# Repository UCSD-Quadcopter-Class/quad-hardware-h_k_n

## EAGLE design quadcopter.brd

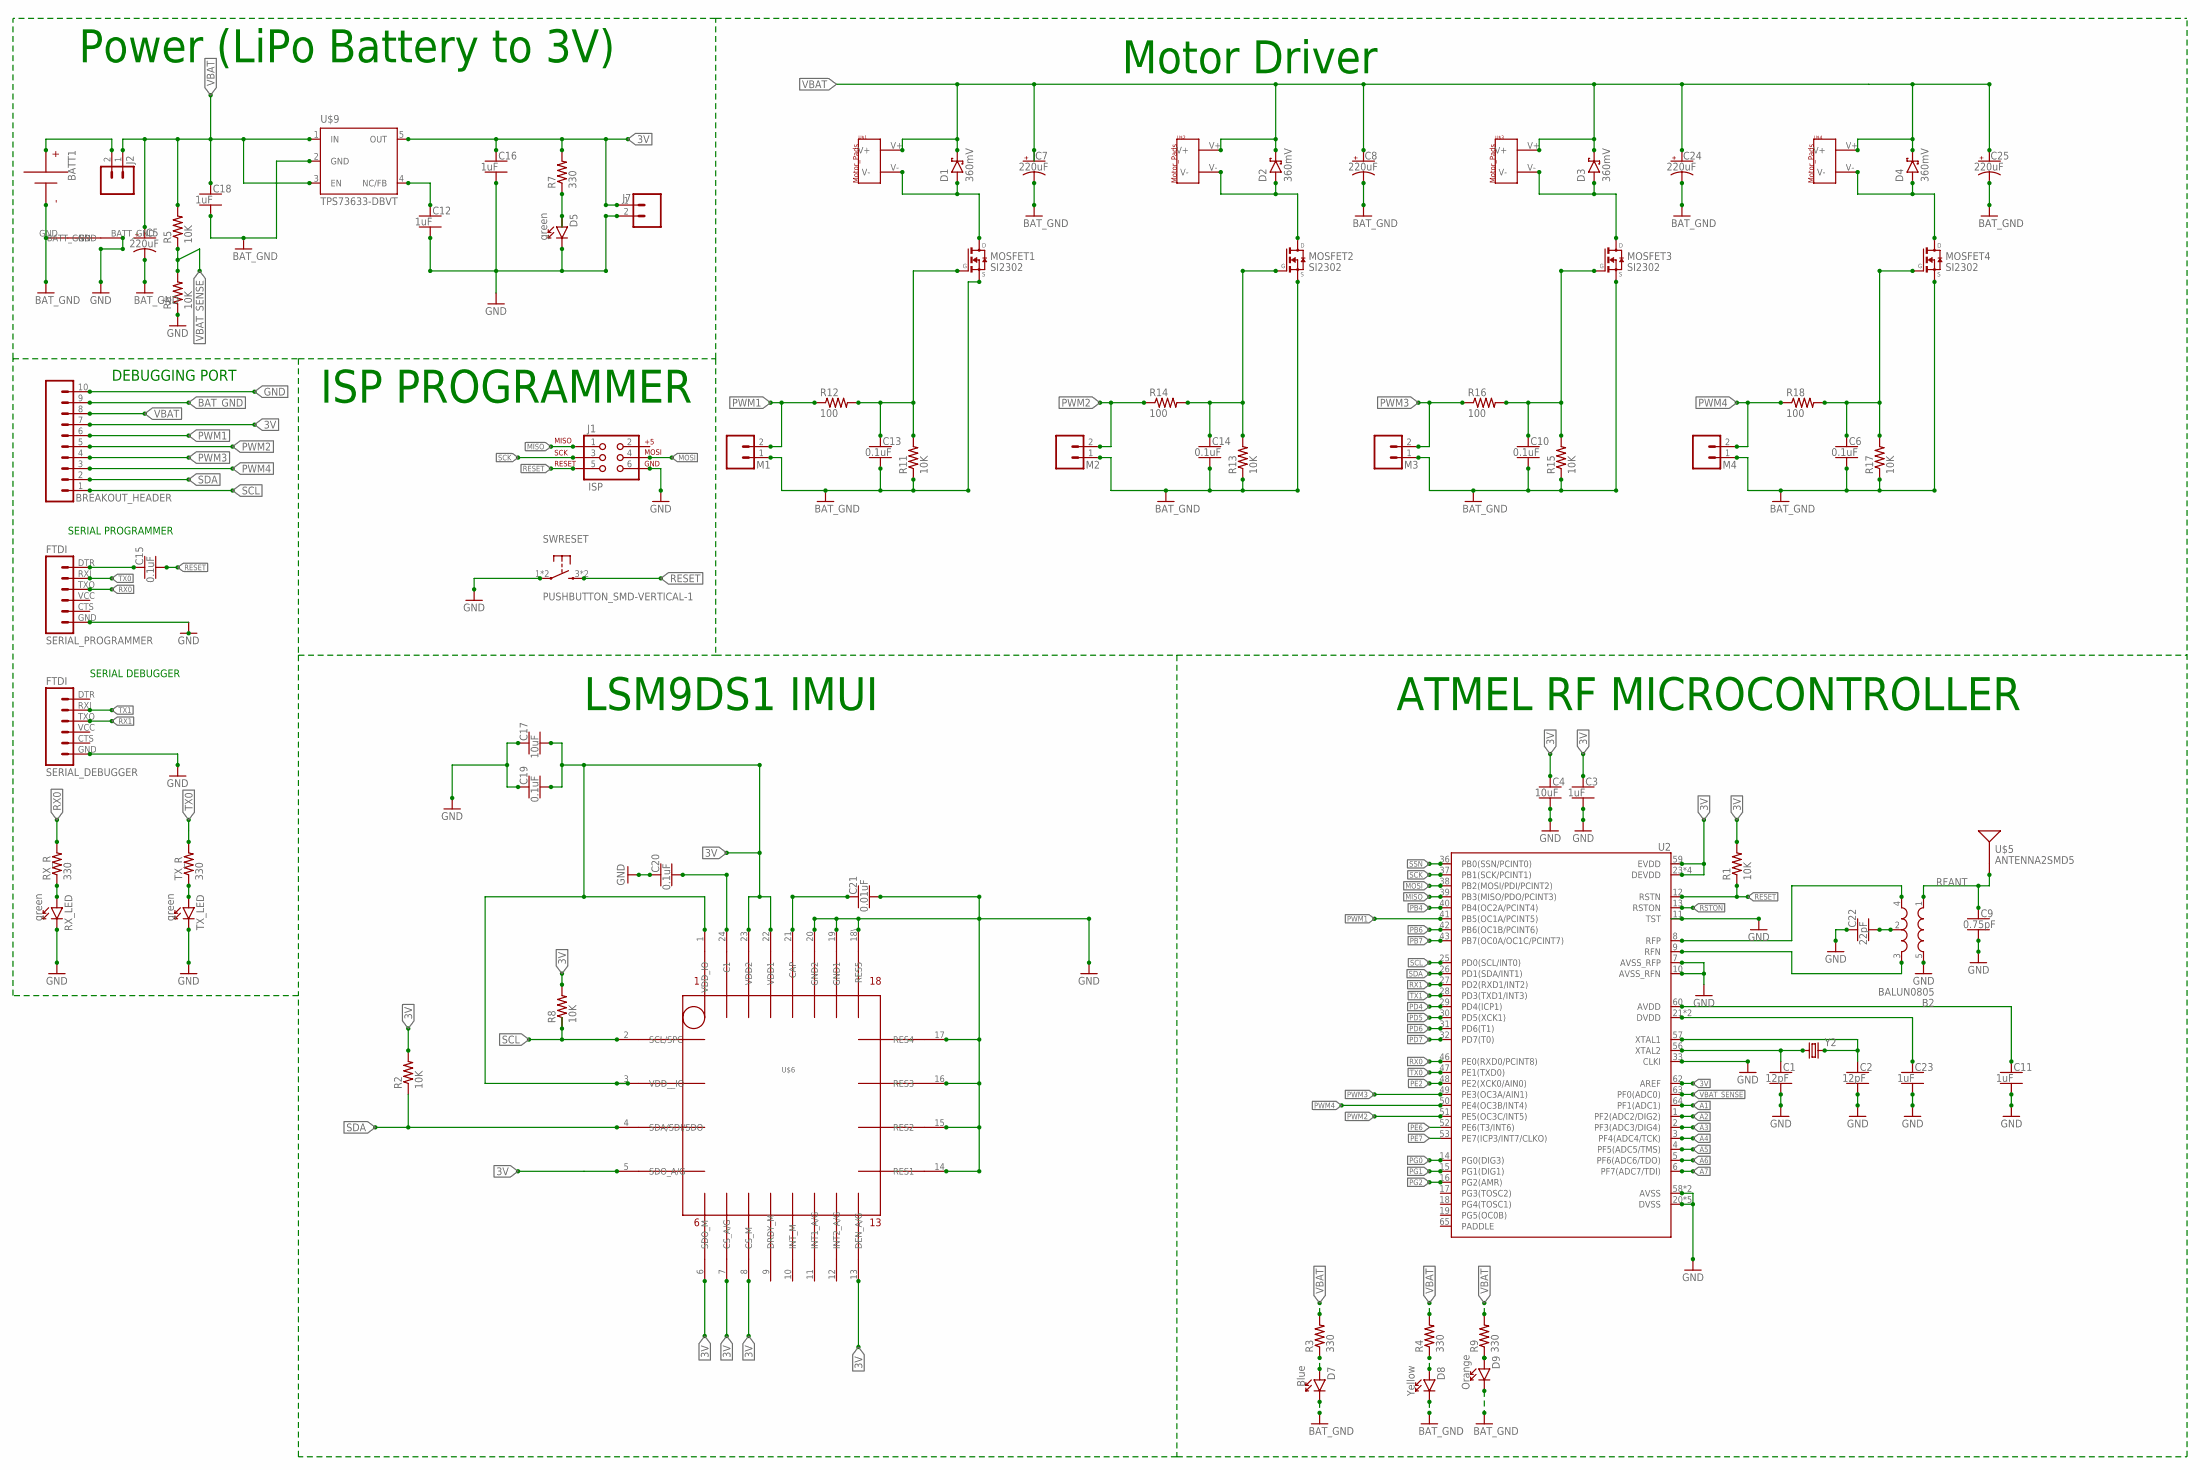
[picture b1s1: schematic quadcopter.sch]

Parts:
B2: BALUN0805; BALUN
BATT1: BATTERY-HUBSAN-W/HOLDER; BATTERY-W/HOLDER-380MAH-HUBSAN
BREAKOUT_HEADER: SIP-10_TH-254X10; HDRV10W63P254_10X1_2540X254H838_HS
C1, C2: 12pF; CAPC2012X140_HS
C3, C11, C12, C16, C18, C23: 1uF; CAPC2012X140_HS
C4, C17: 10uF; CAPC2012X140_HS
C5, C7, C8, C24, C25: 220uF; CAPMP7343X310_HS
C6, C10, C13, C14, C15, C19, C20: 0.1uF; CAPC2012X140_HS
C9: 0.75pF; CAPC2012X140_HS
C21: 0.01uF; CAPC2012X140_HS
C22: 22pF; CAPC2012X140_HS
D1, D2, D3, D4: 360mV; SOD3716X135_HS
D5: green; LEDSC125X200X120-2_HS
D7: Blue; LEDSC125X200X120-2_HS
D8: Yellow; LEDSC125X200X120-2_HS
D9: Orange; LEDSC125X200X120-2_HS
J1: ISP; 2X3-NS
J2, J7: MALE_HEADER_2POS-2X1-0.1IN; MALE_HEADER_2X1_0.1IN
M1, M2, M3, M4: MALE_HEADER_2POS-2X1-0.1IN; MALE_HEADER_2X1_0.1IN
MOSFET1, MOSFET2, MOSFET3, MOSFET4: SI2302; SOT23
R1, R2, R5, R6, R8, R11, R13, R15, R17: 10K; RESC2012X60_HS
R3, R4, R7, R9: 330; RESC2012X60_HS
R12, R14, R16, R18: 100; RESC2012X60_HS
RX_LED: green; LEDSC125X200X120-2_HS
RX_R: 330; RESC2012X60_HS
SERIAL_DEBUGGER: FTDI; FTDI_BASIC
SERIAL_PROGRAMMER: FTDI; FTDI_BASIC
SWRESET: PUSHBUTTON_SMD-VERTICAL-1; TE_FSM8JSMA_HS
TX_LED: green; LEDSC125X200X120-2_HS
TX_R: 330; RESC2012X60_HS
U2: ATMEGA128RFA1; QFN-64
U$1, U$2, U$3, U$4: MOTOR_PADS
U$5: ANTENNA2SMD5; ANTENNA-CHIP5
U$6: IMULAST; LGA-24/4MM
U$7: WIRE_BRIDGE; WIRE_BRIGE
U$9: TPS73633-DBVT; SOT23-DBV
Y2: CRYSTAL5X3; CRYSTAL-SMD-5X3

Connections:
3V: BREAKOUT_HEADER.7, C3.1, C4.1, C16.1, C17.2, C19.2, J7.1, R1.2, R2.2, R7.2, R8.2, U2.23 (DEVDD), U2.34 (DEVDD), U2.44 (DEVDD), U2.54 (DEVDD), U2.59 (EVDD), U2.62 (AREF), U$6.1 (VDD_IO), U$6.3 (VDD__IO), U$6.5 (SDO_A/G), U$6.6 (SDO_M), U$6.7 (CS_A/G), U$6.8 (CS_M), U$6.13 (DEN_A/G), U$6.22 (VDD1), U$6.23 (VDD2), U$9.5 (OUT)
A1: U2.64 (PF1(ADC1))
A2: U2.1 (PF2(ADC2/DIG2))
A3: U2.2 (PF3(ADC3/DIG4))
A4: U2.3 (PF4(ADC4/TCK))
A5: U2.4 (PF5(ADC5/TMS))
A6: U2.5 (PF6(ADC6/TDO))
A7: U2.6 (PF7(ADC7/TDI))
AVDD: C11.1, U2.60 (AVDD)
BAT_GND: BATT1.- (N), BREAKOUT_HEADER.9, C5.2 (-), C6.2, C7.2 (-), C8.2 (-), C10.2, C13.2, C14.2, C18.2, C24.2 (-), C25.2 (-), D7.C, D8.C, D9.C, M1.1, M2.1, M3.1, M4.1, MOSFET1.2 (S), MOSFET2.2 (S), MOSFET3.2 (S), MOSFET4.2 (S), R11.1, R13.1, R15.1, R17.1, U$7.GND, U$9.2 (GND)
DTR: C15.1, SERIAL_PROGRAMMER.DTR (1)
DVDD: C23.1, U2.21 (DVDD), U2.22 (DVDD)
GND: B2.5 (GND), BREAKOUT_HEADER.10, C1.2, C2.2, C3.2, C4.2, C9.2, C11.2, C12.2, C16.2, C17.1, C19.1, C20.1, C21.2, C22.1, C23.2, D5.C, J1.6, J7.2, R6.1, RX_LED.C, SERIAL_DEBUGGER.GND (6), SERIAL_PROGRAMMER.GND (6), SWRESET.1, SWRESET.2 (1), TX_LED.C, U2.7 (AVSS_RFP), U2.10 (AVSS_RFN), U2.11 (TST), U2.20 (DVSS), U2.24 (DVSS), U2.33 (CLKI), U2.35 (DVSS), U2.45 (DVSS), U2.55 (DVSS), U2.58 (AVSS), U2.61 (AVSS), U$6.14 (RES1), U$6.15 (RES2), U$6.16 (RES3), U$6.17 (RES4), U$6.18\ (RES5), U$6.19 (GND1), U$6.20 (GND2), U$7.BATT_GND
MISO: J1.1, U2.39 (PB3(MISO/PDO/PCINT3))
MOSI: J1.4, U2.38 (PB2(MOSI/PDI/PCINT2))
unnamed: C13.1, MOSFET1.1 (G), R11.2, R12.2
unnamed: C2.1, U2.57 (XTAL1), Y2.3 (2)
unnamed: C1.1, U2.56 (XTAL2), Y2.1
unnamed: B2.2 (GND), C22.2
unnamed: D9.A, R9.1
unnamed: D1.A, MOSFET1.3 (D), U$1.V-
unnamed: BATT1.+, J2.2
unnamed: D5.A, R7.1
unnamed: D2.A, MOSFET2.3 (D), U$2.V-
unnamed: TX_LED.A, TX_R.1
unnamed: RX_LED.A, RX_R.1
unnamed: C20.2, U$6.24 (C1)
unnamed: D3.A, MOSFET3.3 (D), U$3.V-
unnamed: C12.1, U$9.4 (NC/FB)
unnamed: D8.A, R4.1
unnamed: D7.A, R3.1
unnamed: D4.A, MOSFET4.3 (D), U$4.V-
unnamed: C21.1, U$6.21 (CAP)
unnamed: C14.1, MOSFET2.1 (G), R13.2, R14.2
unnamed: C10.1, MOSFET3.1 (G), R15.2, R16.2
unnamed: C6.1, MOSFET4.1 (G), R17.2, R18.2
PB4: U2.40 (PB4(OC2A/PCINT4))
PB6: U2.42 (PB6(OC1B/PCINT6))
PB7: U2.43 (PB7(OC0A/OC1C/PCINT7))
PD4: U2.29 (PD4(ICP1))
PD5: U2.30 (PD5(XCK1))
PD6: U2.31 (PD6(T1))
PD7: U2.32 (PD7(T0))
PE2: U2.48 (PE2(XCK0/AIN0))
PE6: U2.52 (PE6(T3/INT6))
PE7: U2.53 (PE7(ICP3/INT7/CLKO))
PG0: U2.14 (PG0(DIG3))
PG1: U2.15 (PG1(DIG1))
PG2: U2.16 (PG2(AMR))
PWM1: BREAKOUT_HEADER.6, M1.2, R12.1, U2.41 (PB5(OC1A/PCINT5))
PWM2: BREAKOUT_HEADER.5, M2.2, R14.1, U2.51 (PE5(OC3C/INT5))
PWM3: BREAKOUT_HEADER.4, M3.2, R16.1, U2.49 (PE3(OC3A/AIN1))
PWM4: BREAKOUT_HEADER.3, M4.2, R18.1, U2.50 (PE4(OC3B/INT4))
RESET: C15.2, J1.5, R1.1, SWRESET.3 (2), SWRESET.4 (2), U2.12 (RSTN)
RFANT: B2.1 (IN), C9.1, U$5.FEED
RFN: B2.3 (OUT2), U2.9 (RFN)
RFP: B2.4 (OUT1), U2.8 (RFP)
RSTON: U2.13 (RSTON)
RX0: RX_R.2, SERIAL_PROGRAMMER.TXO (3), U2.46 (PE0(RXD0/PCINT8))
RX1: SERIAL_DEBUGGER.TXO (3), U2.27 (PD2(RXD1/INT2))
SCK: J1.3, U2.37 (PB1(SCK/PCINT1))
SCL: BREAKOUT_HEADER.1, R8.1, U2.25 (PD0(SCL/INT0)), U$6.2 (SCL/SPC)
SDA: BREAKOUT_HEADER.2, R2.1, U2.26 (PD1(SDA/INT1)), U$6.4 (SDA/SDI/SDO)
SSN: U2.36 (PB0(SSN/PCINT0))
TX0: SERIAL_PROGRAMMER.RXI (2), TX_R.2, U2.47 (PE1(TXD0))
TX1: SERIAL_DEBUGGER.RXI (2), U2.28 (PD3(TXD1/INT3))
VBAT: BREAKOUT_HEADER.8, C5.1 (+), C7.1 (+), C8.1 (+), C18.1, C24.1 (+), C25.1 (+), D1.C, D2.C, D3.C, D4.C, J2.1, R3.2, R4.2, R5.2, R9.2, U$1.V+, U$2.V+, U$3.V+, U$4.V+, U$9.1 (IN), U$9.3 (EN)
VBAT_SENSE: R5.1, R6.2, U2.63 (PF0(ADC0))

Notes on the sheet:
Motor Driver
Power (LiPo Battery to 3V)
ISP PROGRAMMER
DEBUGGING PORT
SERIAL DEBUGGER
SERIAL PROGRAMMER
LSM9DS1 IMUI
ATMEL RF MICROCONTROLLER

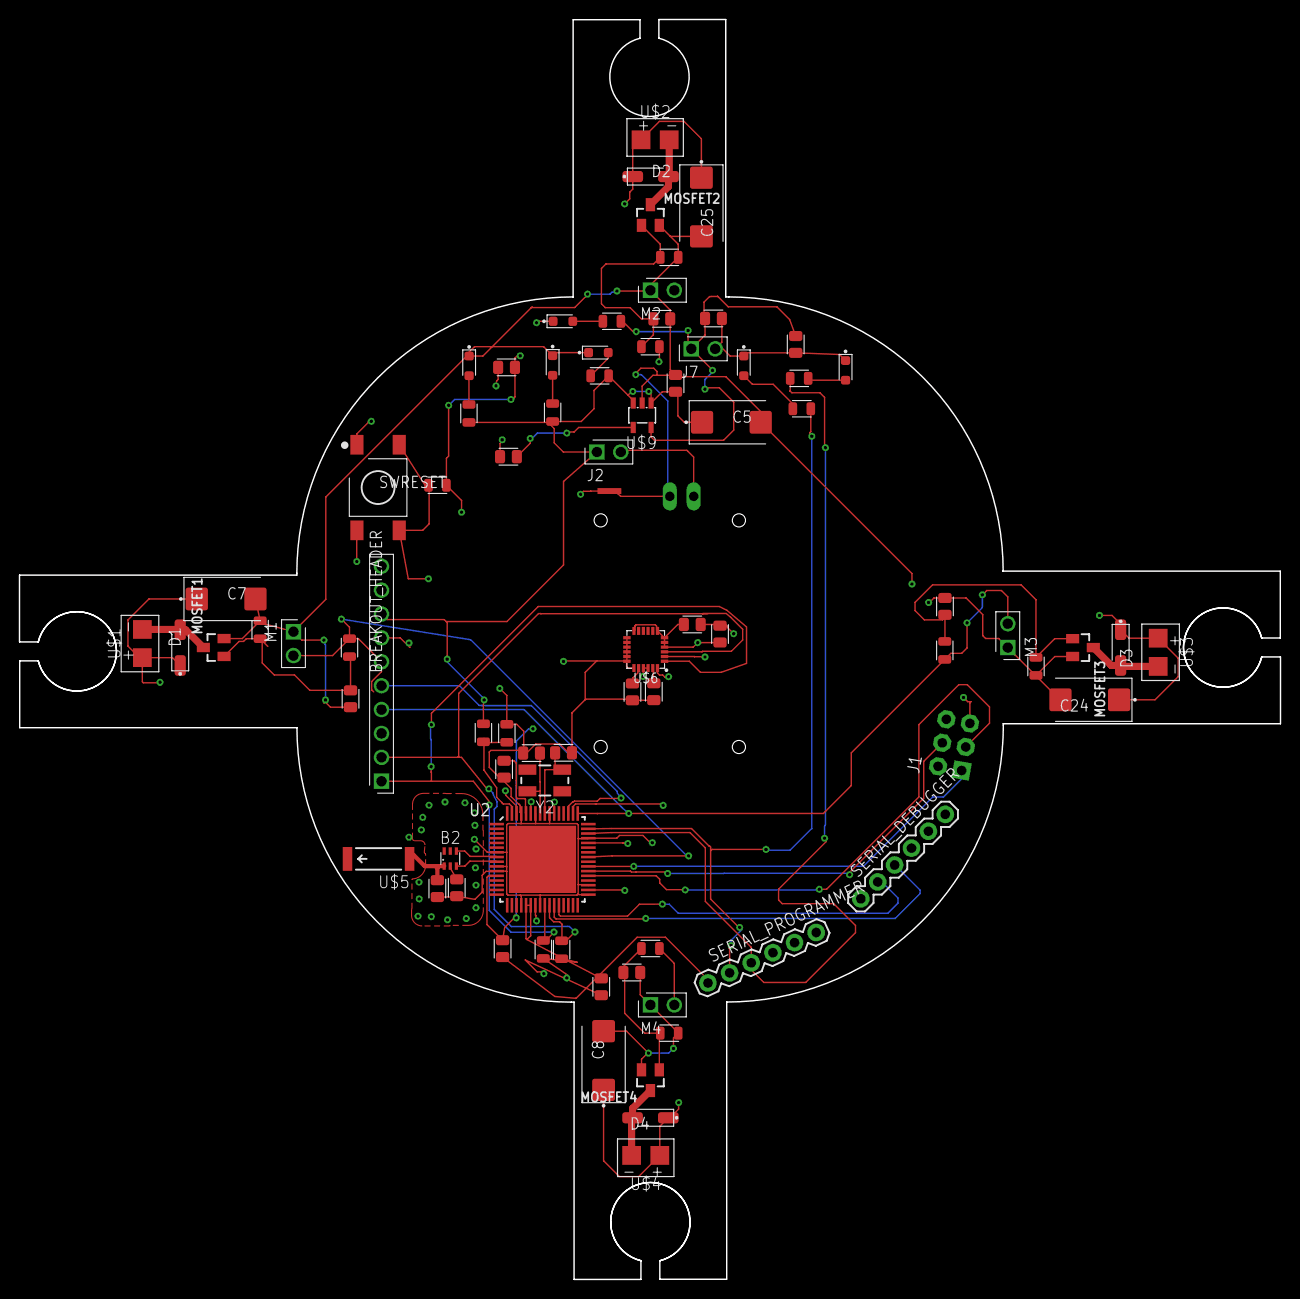
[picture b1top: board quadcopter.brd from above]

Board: 4 copper layers, 134.1 x 134.0 mm, 81 parts (1 on the bottom side), 46 nets.

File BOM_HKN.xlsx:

Part | Value
B2 | BALUN0805
BATT1 | BATTERY-HUBSAN-W/HOLDER
BREAKOUT_HEADER
C1 | 12pF
C2 | 12pF
C3 | 1uF
C4 | 10uF
C5 | 220uF
C6 | 0.1uF
C7 | 220uF
C8 | 220uF
C9 | 0.75pF
C10 | 0.1uF
C11 | 1uF
C12 | 1uF
C13 | 0.1uF
C14 | 0.1uF
C15 | 0.1uF
C16 | 1uF
C17 | 10uF
C18 | 1uF
C19 | 0.1uF
C20 | 0.1uF
C21 | 0.01uF
C22 | 22pF
C23 | 1uF
C24 | 220uF
C25 | 220uF
D1 | 360mV
D2 | 360mV
D3 | 360mV
D4 | 360mV
D5 | green
D7 | Blue
D8 | Yellow
D9 | Orange
J1 | ISP
J2
J7
M1
M2
M3
M4
MOSFET1 | SI2302
MOSFET2 | SI2302
MOSFET3 | SI2302
MOSFET4 | SI2302
R1 | 10K
R2 | 10K
R3 | 330
R4 | 330
R5 | 10K
R6 | 10K
R7 | 330
R8 | 10K
R9 | 330
R11 | 10K
R12 | 100
R13 | 10K
R14 | 100
R15 | 10K
R16 | 100
R17 | 10K
R18 | 100
RX_LED | green
RX_R | 330
SERIAL_DEBUGGER | FTDI
SERIAL_PROGRAMMER | FTDI
SWRESET | PUSHBUTTON_SMD-VERTICAL-1
TX_LED | green
TX_R | 330
U$1 | MOTOR_PADS
U$2 | MOTOR_PADS
U$3 | MOTOR_PADS
U$4 | MOTOR_PADS
U$5 | ANTENNA2SMD5
U$6 | IMULAST
U$7 | WIRE_BRIDGE
U$9 | TPS73633-DBVT
U2 | ATMEGA128RFA1
Y2

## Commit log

2017-04-27 instructior review of original schematic
2017-04-27 fixing repo
2017-05-01 Add files via upload
    Board Layout
2017-05-04 Reviews
2017-05-04 swanson schematic review
2017-05-14 more schematic comments from swanson
2017-05-15 Fixed Schematic but still not able to root 90%
2017-05-17 Route 100% FINALLY.
2017-05-23 CAM-Files
2017-05-23 board comments from swanson
2017-05-25 After fixing professor's comments
2017-05-27 more board comments from swanson
2017-05-29 After fixing professor's comments V2
2017-05-29 After fixing professor's comments V3
2017-05-29 After fixing professor's comments V3 (Fixed wires)
2017-05-30 After fixing professor's comments V4 (GND)

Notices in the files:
parts and their libraries:
SparkFun-Connectors: Licensing: CC v3.0 Share-Alike You are welcome to use this library for commercial purposes.
